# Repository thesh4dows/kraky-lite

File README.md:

# Kraky-lite

Kraky lite is a smaller version of kraky focused only on wifi, bluetooth and sub-GHz frequencies.
I've decided to do it so i can learn SMD sodering with a simpler project. 
This project can be used for learning the basics of wifi, bluetooth and sub-GHz frequencies attacks and protections.

---

## Main Components

| Function | Component |
|--------|----------|
| Logic board | **ESP32-S3 N16R8** |
| Sub-GHz | **CC1101** |
| Wifi/bluetooth | **NFR24L01** |
| Display | **TFT Display** |

---

## Future Features 

- microSD support

---

## WIRING DIAGRAM

---

## PCB 

---

## PCB AND 3D RENDER COMBINED

---

## BOM LIST
| Component | Link |
|--------|----------|
| **ESP32-S3-N16R8** | [Aliexpress](https://it.aliexpress.com/item/1005006214506085.html?spm=a2g0o.productlist.main.34.42beDNGcDNGcGn&algo_pvid=c7ebd4d1-f37e-43e0-8528-b76b49bbafec&algo_exp_id=c7ebd4d1-f37e-43e0-8528-b76b49bbafec-33&pdp_ext_f=%7B%22order%22%3A%22237%22%2C%22eval%22%3A%221%22%2C%22fromPage%22%3A%22search%22%7D&pdp_npi=6%40dis%21EUR%214.39%214.39%21%21%215.04%215.04%21%40211b80c217716672677421292e2da6%2112000036313776249%21sea%21IT%214906144315%21X%211%210%21n_tag%3A-29919%3Bd%3Af5869dfc%3Bm03_new_user%3A-29895&curPageLogUid=DdOQtJzkOMgO&utparam-url=scene%3Asearch%7Cquery_from%3A%7Cx_object_id%3A1005006214506085%7C_p_origin_prod%3A) | 
| **buttons** | [Aliexpress](https://it.aliexpress.com/item/1005003751942617.html?spm=a2g0o.productlist.main.6.7b66UgMCUgMC2v&algo_pvid=90b119e5-116b-44ca-8d19-1b1e01badc9a&algo_exp_id=90b119e5-116b-44ca-8d19-1b1e01badc9a-5&pdp_ext_f=%7B%22order%22%3A%22457%22%2C%22eval%22%3A%221%22%2C%22fromPage%22%3A%22search%22%7D&pdp_npi=6%40dis%21EUR%212.68%212.32%21%21%2121.57%2118.69%21%40211b618e17694579682652136e0d37%2112000027951043689%21sea%21IT%214906144315%21X%211%210%21n_tag%3A-29919%3Bd%3Af5869dfc%3Bm03_new_user%3A-29895%3BpisId%3A5000000198855826&curPageLogUid=h3YPZfgd06kE&utparam-url=scene%3Asearch%7Cquery_from%3A%7Cx_object_id%3A1005003751942617%7C_p_origin_prod%3A) |
| **tft display** | [Aliexpress](https://www.aliexpress.com/item/1005009234839022.html) |
| **10k ohm** | [Aliexpress](https://it.aliexpress.com/item/1005008049421850.html?spm=a2g0o.productlist.main.5.339e2072xf4Fp6&algo_pvid=60a0f9d2-cb3a-4061-b250-3a89b5594825&algo_exp_id=60a0f9d2-cb3a-4061-b250-3a89b5594825-4&pdp_ext_f=%7B%22order%22%3A%221081%22%2C%22eval%22%3A%221%22%2C%22fromPage%22%3A%22search%22%7D&pdp_npi=6%40dis%21EUR%212.03%211.29%21%21%2116.36%2110.40%21%40211b61bb17694589696196228e2a30%2112000043433742591%21sea%21IT%214906144315%21X%211%210%21n_tag%3A-29919%3Bd%3Af5869dfc%3Bm03_new_user%3A-29895%3BpisId%3A5000000198855826&curPageLogUid=0AoDAOfCkDU4&utparam-url=scene%3Asearch%7Cquery_from%3A%7Cx_object_id%3A1005008049421850%7C_p_origin_prod%3A) |
| **5.1K ohm** | [Aliexpress](https://it.aliexpress.com/item/1005002705550504.html?spm=a2g0o.productlist.main.1.1aa2xZ7pxZ7p1I&algo_pvid=4709e6db-5db9-4b2b-922c-cc912aef84b5&algo_exp_id=4709e6db-5db9-4b2b-922c-cc912aef84b5-0&pdp_ext_f=%7B%22order%22%3A%222719%22%2C%22eval%22%3A%221%22%2C%22fromPage%22%3A%22search%22%7D&pdp_npi=6%40dis%21EUR%211.33%211.33%21%21%211.53%211.53%21%40211b80c217716675645392862e2ded%2112000021795176620%21sea%21IT%214906144315%21X%211%210%21n_tag%3A-29919%3Bd%3Af5869dfc%3Bm03_new_user%3A-29895&curPageLogUid=qzURhFrHFgME&utparam-url=scene%3Asearch%7Cquery_from%3A%7Cx_object_id%3A1005002705550504%7C_p_origin_prod%3A) |
| **am51117-3.3** | [Aliexpress](https://it.aliexpress.com/item/1005002487704059.html?spm=a2g0o.productlist.main.3.5e37L8QTL8QTQh&aem_p4p_detail=20260221015318585911214270720010847834&algo_pvid=ea4f2d53-853f-4e96-b1d1-080e2c659de5&algo_exp_id=ea4f2d53-853f-4e96-b1d1-080e2c659de5-3&pdp_ext_f=%7B%22order%22%3A%223661%22%2C%22eval%22%3A%221%22%2C%22fromPage%22%3A%22search%22%7D&pdp_npi=6%40dis%21EUR%211.93%211.93%21%21%212.22%212.22%21%40211b441e17716675983814641e9297%2112000020837902169%21sea%21IT%214906144315%21X%211%210%21n_tag%3A-29919%3Bd%3Af5869dfc%3Bm03_new_user%3A-29895&curPageLogUid=6WlvmG2NNVx1&utparam-url=scene%3Asearch%7Cquery_from%3A%7Cx_object_id%3A1005002487704059%7C_p_origin_prod%3A&search_p4p_id=20260221015318585911214270720010847834_1) |
| **2345986-1** | [Aliexpress](https://it.aliexpress.com/item/1005007419369264.html?spm=a2g0o.productlist.main.4.4508u2MKu2MK3q&aem_p4p_detail=2026022101542414472877640010640013303716&algo_pvid=f6b0fa28-2c20-49bd-9f15-d53680192fef&algo_exp_id=f6b0fa28-2c20-49bd-9f15-d53680192fef-3&pdp_ext_f=%7B%22order%22%3A%227494%22%2C%22spu_best_type%22%3A%22price%22%2C%22eval%22%3A%221%22%2C%22fromPage%22%3A%22search%22%7D&pdp_npi=6%40dis%21EUR%211.86%211.79%21%21%212.14%212.06%21%40211b61a417716676646955855e5d10%2112000040675429659%21sea%21IT%214906144315%21X%211%210%21n_tag%3A-29919%3Bd%3Af5869dfc%3Bm03_new_user%3A-29895&curPageLogUid=mCOWM8LKrjb6&utparam-url=scene%3Asearch%7Cquery_from%3A%7Cx_object_id%3A1005007419369264%7C_p_origin_prod%3A&search_p4p_id=2026022101542414472877640010640013303716_1) |
| **100nF** | [Aliexpress](https://it.aliexpress.com/item/1005005691676032.html?spm=a2g0o.cart.0.0.1eb718fcbElXUV&mp=1&pdp_npi=6%40dis%21EUR%21EUR%202.24%21EUR%201.31%21%21EUR%201.31%21%21%21%4021038e1e17694577658065675ead3b%2112000034022594969%21ct%21IT%214906144315%21%211%210%21&gatewayAdapt=glo2ita) |
| **10uF** | [Aliexpress](https://it.aliexpress.com/item/1005011610443745.html?spm=a2g0o.productlist.main.19.44c8f5fff5ffPq&algo_pvid=52247e1d-eb32-4d5c-b3f6-5517e39c67bf&algo_exp_id=52247e1d-eb32-4d5c-b3f6-5517e39c67bf-18&pdp_ext_f=%7B%22order%22%3A%2211%22%2C%22eval%22%3A%221%22%2C%22fromPage%22%3A%22search%22%7D&pdp_npi=6%40dis%21EUR%213.86%211.44%21%21%2130.54%2111.38%21%40211b61a417716728296248882e5d0b%2112000056051812861%21sea%21IT%214906144315%21X%211%210%21n_tag%3A-29919%3Bd%3Af5869dfc%3Bm03_new_user%3A-29895%3BpisId%3A5000000200414378&curPageLogUid=OsI94ufdQ7ZQ&utparam-url=scene%3Asearch%7Cquery_from%3A%7Cx_object_id%3A1005011610443745%7C_p_origin_prod%3A) |
| **2x4 pin holder** | [Aliexpress](https://it.aliexpress.com/item/1005007049075918.html?spm=a2g0o.productlist.main.14.579bKNQXKNQX6b&algo_pvid=294263cc-7d5a-49ec-819e-e1e74a3b1e3e&algo_exp_id=294263cc-7d5a-49ec-819e-e1e74a3b1e3e-13&pdp_ext_f=%7B%22order%22%3A%22107%22%2C%22eval%22%3A%221%22%2C%22fromPage%22%3A%22search%22%7D&pdp_npi=6%40dis%21EUR%211.92%211.92%21%21%2115.27%2115.27%21%40211b6c1917714046123557689e7773%2112000039229446462%21sea%21IT%214906144315%21X%211%210%21n_tag%3A-29919%3Bd%3Af5869dfc%3Bm03_new_user%3A-29895&curPageLogUid=65bfxIdz91Fv&utparam-url=scene%3Asearch%7Cquery_from%3A%7Cx_object_id%3A1005007049075918%7C_p_origin_prod%3A) |
| **CC1101** | [Aliexpress](https://it.aliexpress.com/item/1005005200440286.html?spm=a2g0o.detail.0.0.112dwyOYwyOYtb&mp=1&pdp_npi=6%40dis%21EUR%21EUR%202.83%21EUR%202.81%21%21EUR%202.81%21%21%21%40211b61bb17717580744617886e19b5%2112000044897164169%21ct%21IT%214906144315%21%211%210%21&_gl=1*1wobrbm*_gcl_aw*R0NMLjE3NzE1MjQ2MjYuQ2owS0NRaUFodHZNQmhEQkFSSXNBTDI2cGpHM1ZRa1BoUll1SDBSSE40Ykh5bUF1RlpMbEVKQmtiYS00QVZJcVRIcXBFSTZHOGtwWkEtd2FBa3RURUFMd193Y0I.*_gcl_dc*R0NMLjE3NzE1MjQ2MjYuQ2owS0NRaUFodHZNQmhEQkFSSXNBTDI2cGpHM1ZRa1BoUll1SDBSSE40Ykh5bUF1RlpMbEVKQmtiYS00QVZJcVRIcXBFSTZHOGtwWkEtd2FBa3RURUFMd193Y0I.*_gcl_au*MTcxMjAzMTA0LjE3NzE1MjQ2MjU.*_ga*MTEzNzE4MTYwMTA1MjIyMS4xNzI2NTAwNTQ2NTA5*_ga_VED1YSGNC7*czE3NzE3NTQ2MjIkbzQwJGcxJHQxNzcxNzU4MDc1JGo2MCRsMCRoMA..&gatewayAdapt=glo2ita) |
| **NFR24L01** | [Aliexpress](https://it.aliexpress.com/item/1005009048175597.html?spm=a2g0o.productlist.main.6.6e5f405abHx9sc&algo_pvid=10def4a3-4e20-4bd2-94f3-d9d95d597536&algo_exp_id=10def4a3-4e20-4bd2-94f3-d9d95d597536-5&pdp_ext_f=%7B%22order%22%3A%22256%22%2C%22spu_best_type%22%3A%22price%22%2C%22eval%22%3A%221%22%2C%22fromPage%22%3A%22search%22%7D&pdp_npi=6%40dis%21EUR%212.42%212.42%21%21%2119.17%2119.17%21%40210391a017717579682301728e9a81%2112000047706967396%21sea%21IT%214906144315%21X%211%210%21n_tag%3A-29919%3Bd%3Af5869dfc%3Bm03_new_user%3A-29895&curPageLogUid=PTz4PpO0x6AV&utparam-url=scene%3Asearch%7Cquery_from%3A%7Cx_object_id%3A1005009048175597%7C_p_origin_prod%3A) |

---

## Responsible Use

Kraky lite is built to make it easier for anyone to explore and understand how multifunction electronic devices work in everyday life.
It’s not intended for bypassing security systems or breaking any laws.

All features are implemented with an educational and experimental focus.

---

## Tools Used

- KiCad 9
- Fusion360
- PlatformIO

---

## Project Status

This project is **work in progress (WIP)**.  
Future updates will include:

- microSD implementation
- firmware development

---

## Contributing

Kraky lite is an **open and educational project**.  
Feedback, suggestions, and improvements are always welcome.

---

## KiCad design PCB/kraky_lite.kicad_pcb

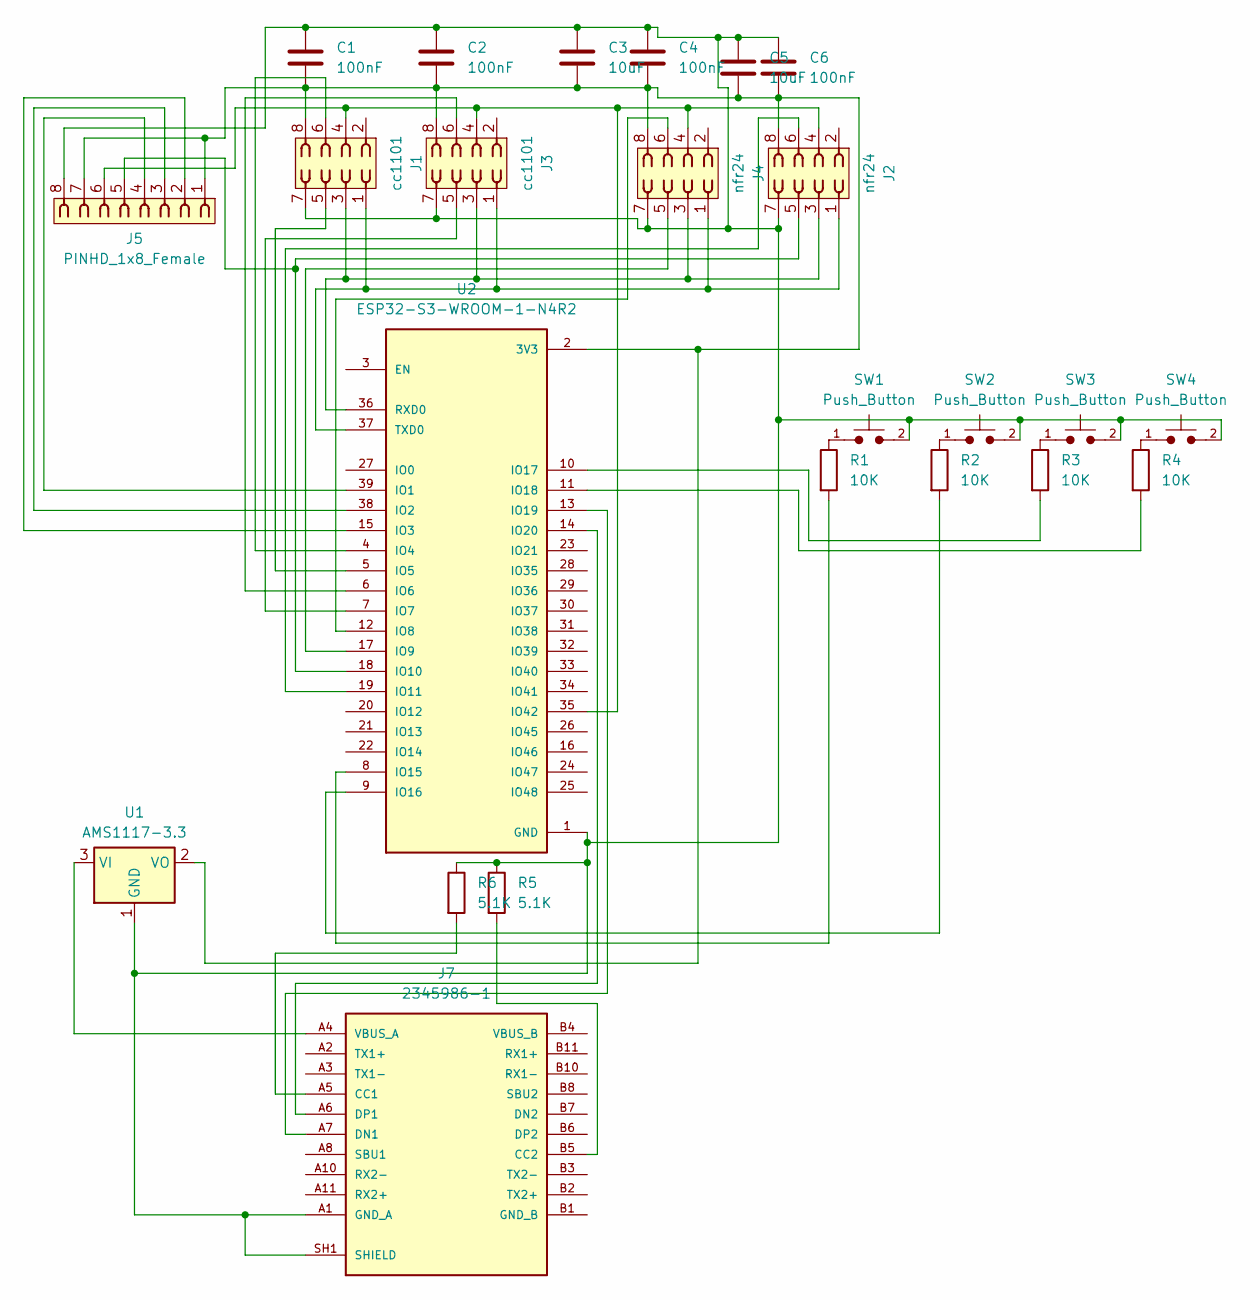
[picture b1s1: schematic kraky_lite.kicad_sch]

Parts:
C1, C2, C4, C6: 100nF; C_Axial_L3.8mm_D2.6mm_P7.50mm_Horizontal
C3, C5: 10uF; C_Axial_L3.8mm_D2.6mm_P7.50mm_Horizontal
J1, J3: cc1101; PinSocket_2x04_P2.54mm_Vertical
J2, J4: nfr24; PinSocket_2x04_P2.54mm_Vertical
J5: PINHD_1x8_Female; PinSocket_1x08_P2.54mm_Vertical
J7: 2345986-1; TE_2345986-1; PARTREV C
R1, R2, R3, R4: 10K; R_Axial_DIN0204_L3.6mm_D1.6mm_P5.08mm_Horizontal
R5, R6: 5.1K; R_Axial_DIN0204_L3.6mm_D1.6mm_P5.08mm_Horizontal
SW1, SW2, SW3, SW4: Push_Button; SW_PUSH_6mm
U1: AMS1117-3.3; SOT-223-3_TabPin2
U2: ESP32-S3-WROOM-1-N4R2; XCVR_ESP32-S3-WROOM-1-N4R2; PARTREV v1.0

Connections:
GND: C1.1, C2.1, C3.1, C4.1, C5.1, C6.1, J1.7, J2.7, J3.7, J4.7, J5.8, J7.A1 (GND_A), J7.A12 (GND_A), J7.SH1 (SHIELD), J7.SH2 (SHIELD), J7.SH3 (SHIELD), J7.SH4 (SHIELD), R5.1, R6.1, SW1.2, SW2.2, SW3.2, SW4.2, U1.1 (GND), U2.1 (GND), U2.40 (GND), U2.41_1 (GND), U2.41_2 (GND), U2.41_3 (GND), U2.41_4 (GND), U2.41_5 (GND), U2.41_6 (GND), U2.41_7 (GND), U2.41_8 (GND), U2.41_9 (GND)
GND_B: J7.B1 (GND_B), J7.B12 (GND_B)
unnamed: J7.A5 (CC1), R6.2
unnamed: J7.B5 (CC2), R5.2
unnamed: J7.A7 (DN1), U2.13 (IO19)
unnamed: J7.A6 (DP1), U2.14 (IO20)
unnamed: R1.1, SW1.1
unnamed: R2.1, SW2.1
unnamed: R3.1, SW3.1
unnamed: R4.1, SW4.1
unnamed: C1.2, C2.2, C3.2, C4.2, C5.2, C6.2, J1.8, J2.8, J3.8, J4.8, J5.1, J5.7, U1.2 (VO), U2.2 (3V3)
unnamed: J5.4, U2.39 (IO1)
unnamed: J5.3, U2.38 (IO2)
unnamed: J5.2, U2.15 (IO3)
unnamed: J1.6, U2.4 (IO4)
unnamed: J1.5, U2.5 (IO5)
unnamed: J3.6, U2.6 (IO6)
unnamed: J3.5, U2.7 (IO7)
unnamed: J4.6, U2.12 (IO8)
unnamed: J4.5, U2.17 (IO9)
unnamed: J2.5, J5.5, U2.18 (IO10)
unnamed: J2.6, U2.19 (IO11)
unnamed: R1.2, U2.8 (IO15)
unnamed: R2.2, U2.9 (IO16)
unnamed: R3.2, U2.10 (IO17)
unnamed: R4.2, U2.11 (IO18)
unnamed: J1.4, J2.4, J3.4, J4.4, J5.6, U2.35 (IO42)
unnamed: J1.3, J2.3, J3.3, J4.3, U2.36 (RXD0)
unnamed: J1.1, J2.1, J3.1, J4.1, U2.37 (TXD0)
VBUS_A: J7.A4 (VBUS_A), J7.A9 (VBUS_A), U1.3 (VI)
VBUS_B: J7.B4 (VBUS_B), J7.B9 (VBUS_B)

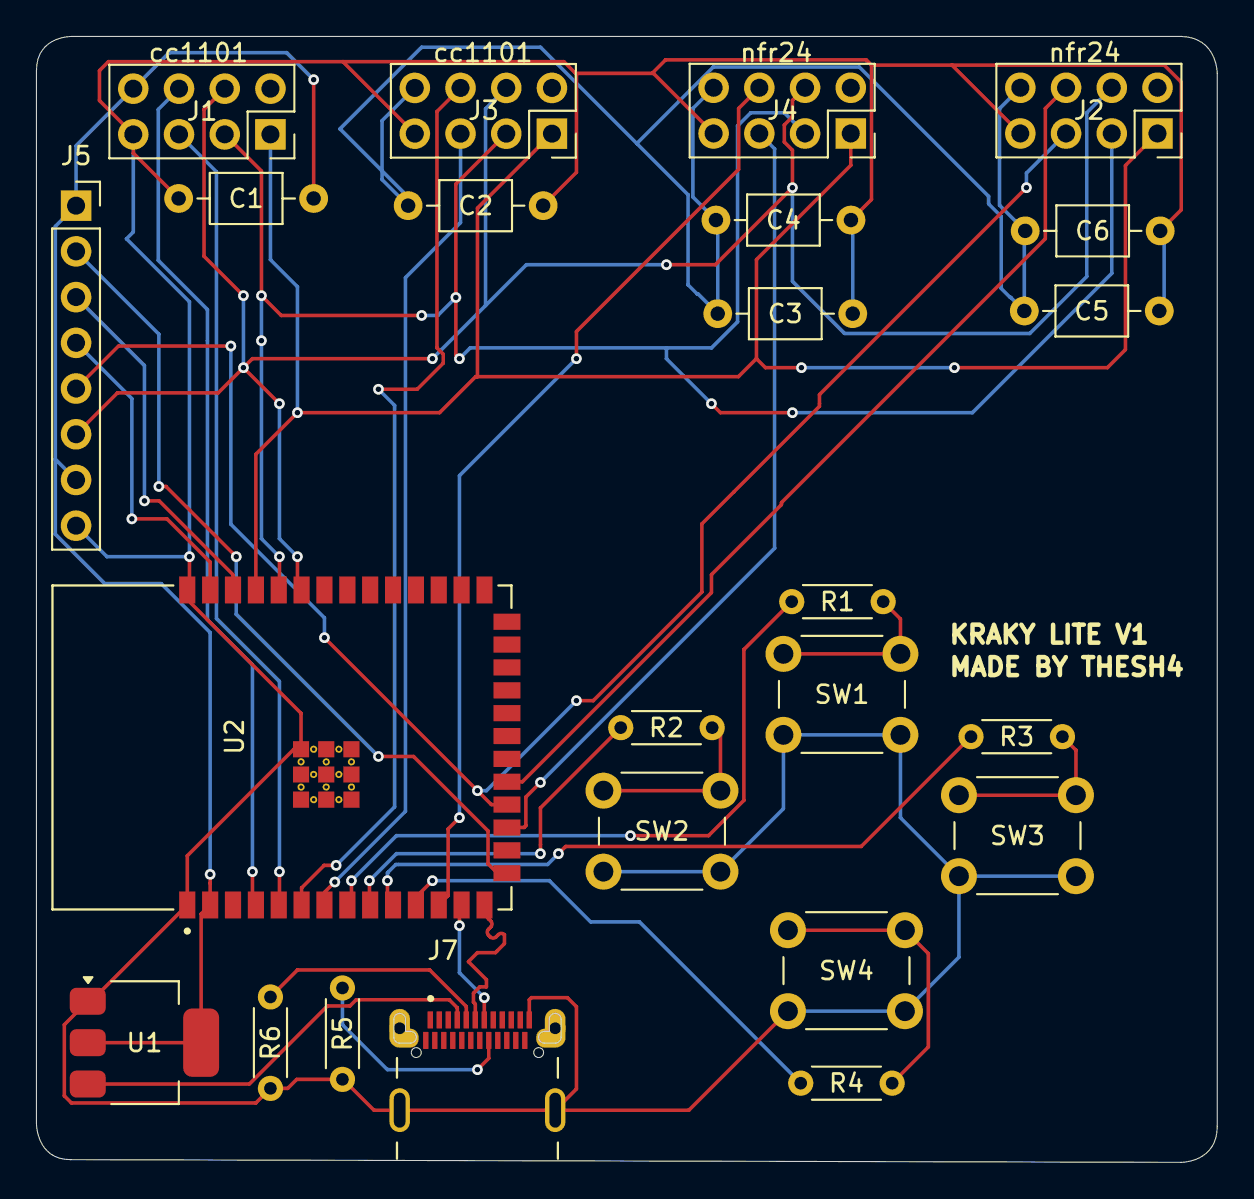
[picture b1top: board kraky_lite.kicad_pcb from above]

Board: 2 copper layers, 65.6 x 62.6 mm, 24 parts (0 on the bottom side), 31 nets.

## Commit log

2026-02-15 Create ba
2026-02-15 Create bva
